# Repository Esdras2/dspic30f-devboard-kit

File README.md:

# dsPIC30F4011 / dsPIC33EP Dev Boards  
*A through-hole, single-supply platform for mixed-signal DSP labs*

> Compact, **breadboard-friendly** boards built around Microchip’s  
> **dsPIC30F4011 (DIP-40)** and **dsPIC33EP128MC206 (TQFP-64)**.  
> Ideal for university courses and hobbyists who need a low-cost, fully-THT solution for real-time DSP, motor-control, or instrumentation projects.

---

## 📑 Table of Contents
1. [Key Features (Rev D)](#key-features-rev-d)  
2. [Hardware Revisions](#hardware-revisions)  
3. [Folder Structure](#folder-structure)  
4. [Quick Start](#quick-start)  
5. [Bill of Materials](#bill-of-materials)  
6. [Pinout Reference](#pinout-reference)  
7. [Contributing](#contributing)  
8. [License](#license)  
9. [Resumen rápido en español](#resumen-rápido-en-español)

---

## Key Features (Rev D)

| Block            | Details                                                                                                     |
|------------------|-------------------------------------------------------------------------------------------------------------|
| **Power**        | 12 V DC barrel jack → **on-board 5 V LDO** (LM7805)                                                         |
| **CPU**          | **dsPIC30F4011** (DIP-40) or **dsPIC33EP128MC206** (TQFP-64, see docs)                                      |
| **Clock**        | Precise UART/DSP timing                                                                                     |
| **Reset**        | Single **RC + Schmitt trigger** → faster boot, ~50 % parts count cut                                        |
| **ICSP**         | Standard 6-pin header (Pickit 3/4 compatible)                                                               |
| **Service**      | **Bridge jumpers** isolate power, ICSP, and analog rails → safe bring-up / troubleshooting                   |
| **Silkscreen**   | Pin name on **every** MCU pad + labelled test points                                                        |
| **Form Factor**  | 52 mm × 45 mm PCB (≈18 % smaller than Rev B) — fits 70 mm breadboards                                       |

*Full schematic, 3-D renders, PDFs, and Gerbers live in `/hardware/Rev_D/`.*

---

## Hardware Revisions

| Rev | Focus                      | Major Changes                                                                                                          |
|-----|----------------------------|------------------------------------------------------------------------------------------------------------------------|
| **B** | First production           | Base THT design, 12 V→5 V regulation, full silkscreen                                                                  |
| **C** | Bug-fix & size reduction  | Fixed reversed barrel polarity, wired V<sub>REF±</sub>; **PCB shrunk** 63 × 52 mm → 52 × 45 mm                          |
| **D** | Serviceability & accuracy | Simplified reset, **larger socket pads**, bridge jumpers, **crystal oscillator added**                                 |

*Older spins remain for reference; **Rev D** is the recommended build.*

---

## Folder Structure
```text
.
├── hardware/         # KiCad 8 projects
│   ├── Rev_B/
│   ├── Rev_C/
│   └── Rev_D/
├── firmware/         # MPLAB X XC16 demo code (blinky, UART loop-back, FIR demo)
├── docs/             # Schematics (PDF), BOMs (CSV/XLSX), 3-D STEP, pinouts
│   └── dspic33.cvs   # Pinout for dsPIC33EP128MC206
└── README.md
```

---

## Quick Start

### 1 · Clone & Open Hardware

```bash
git clone https://github.com/<your-org>/dsPIC30F4011-THT.git
cd dsPIC30F4011-THT/hardware/Rev_D
kicad Rev_D.kicad_pro    # KiCad ≥ 8.0
```

### 2 · Generate Gerbers

KiCad → **File ▸ Plot** → select *Gerber* + *Drill*; zip and send to JLCPCB / PCBWay / OSH Park.

### 3 · Assemble

All parts are **through-hole**; ideal for hand-soldering or wave machines.  
*Tip :* keep bridge jumpers **open** on first power-up.

### 4 · Flash the Demo

TBD

---

## Bill of Materials (excerpt)

| Qty | Designator | Part & Link         | Note                 |
| --- | ---------- | ------------------- | -------------------- |
| 1   | U1         | dsPIC30F4011-I/P    | 40-pin DIP, 30 MIPS  |
| 1   | X1         | Crystal 7 .3728 MHz | HC-49S               |
| 2   | C7, C8     | 22 pF NP0           | Crystal load caps    |
| 1   | IC1        | LM7805              | TO-220, 1 A          |
| 8   | C1…C8      | 100 nF MLCC         | Decoupling (per VDD) |

*See* `docs/BOM_Rev_D.xlsx` *for the full list with supplier SKUs.*

---

## Pinout Reference

- **dsPIC30F4011**: See schematic and silkscreen.
- **dsPIC33EP128MC206**:  
  Pinout available in [`docs/dspic33.cvs`](docs/dspic33.cvs):

  ```
  1,(RA7)
  2,(RB14)
  3,(RB15)
  ...
  64,(RA10)
  ```

---

## Contributing
TBD

Bug reports and board mods are welcome!

---

## License

All hardware, firmware, and documents are released under the **MIT License**.  
See the [LICENSE](LICENSE) file for details.

---

## Resumen rápido (español)

* Placa educativa **THT** con **dsPIC30F4011** y soporte para **dsPIC33EP128MC206**.
* Rev D añade cristal, jumpers de aislamiento y pads más amplios.
* Archivos KiCad 8 en `/hardware/Rev_D/`; BOM completa y pinout en `docs/`.
* Programación vía ICSP con Pickit 3/4.

¡Felices prototipos! 🎉

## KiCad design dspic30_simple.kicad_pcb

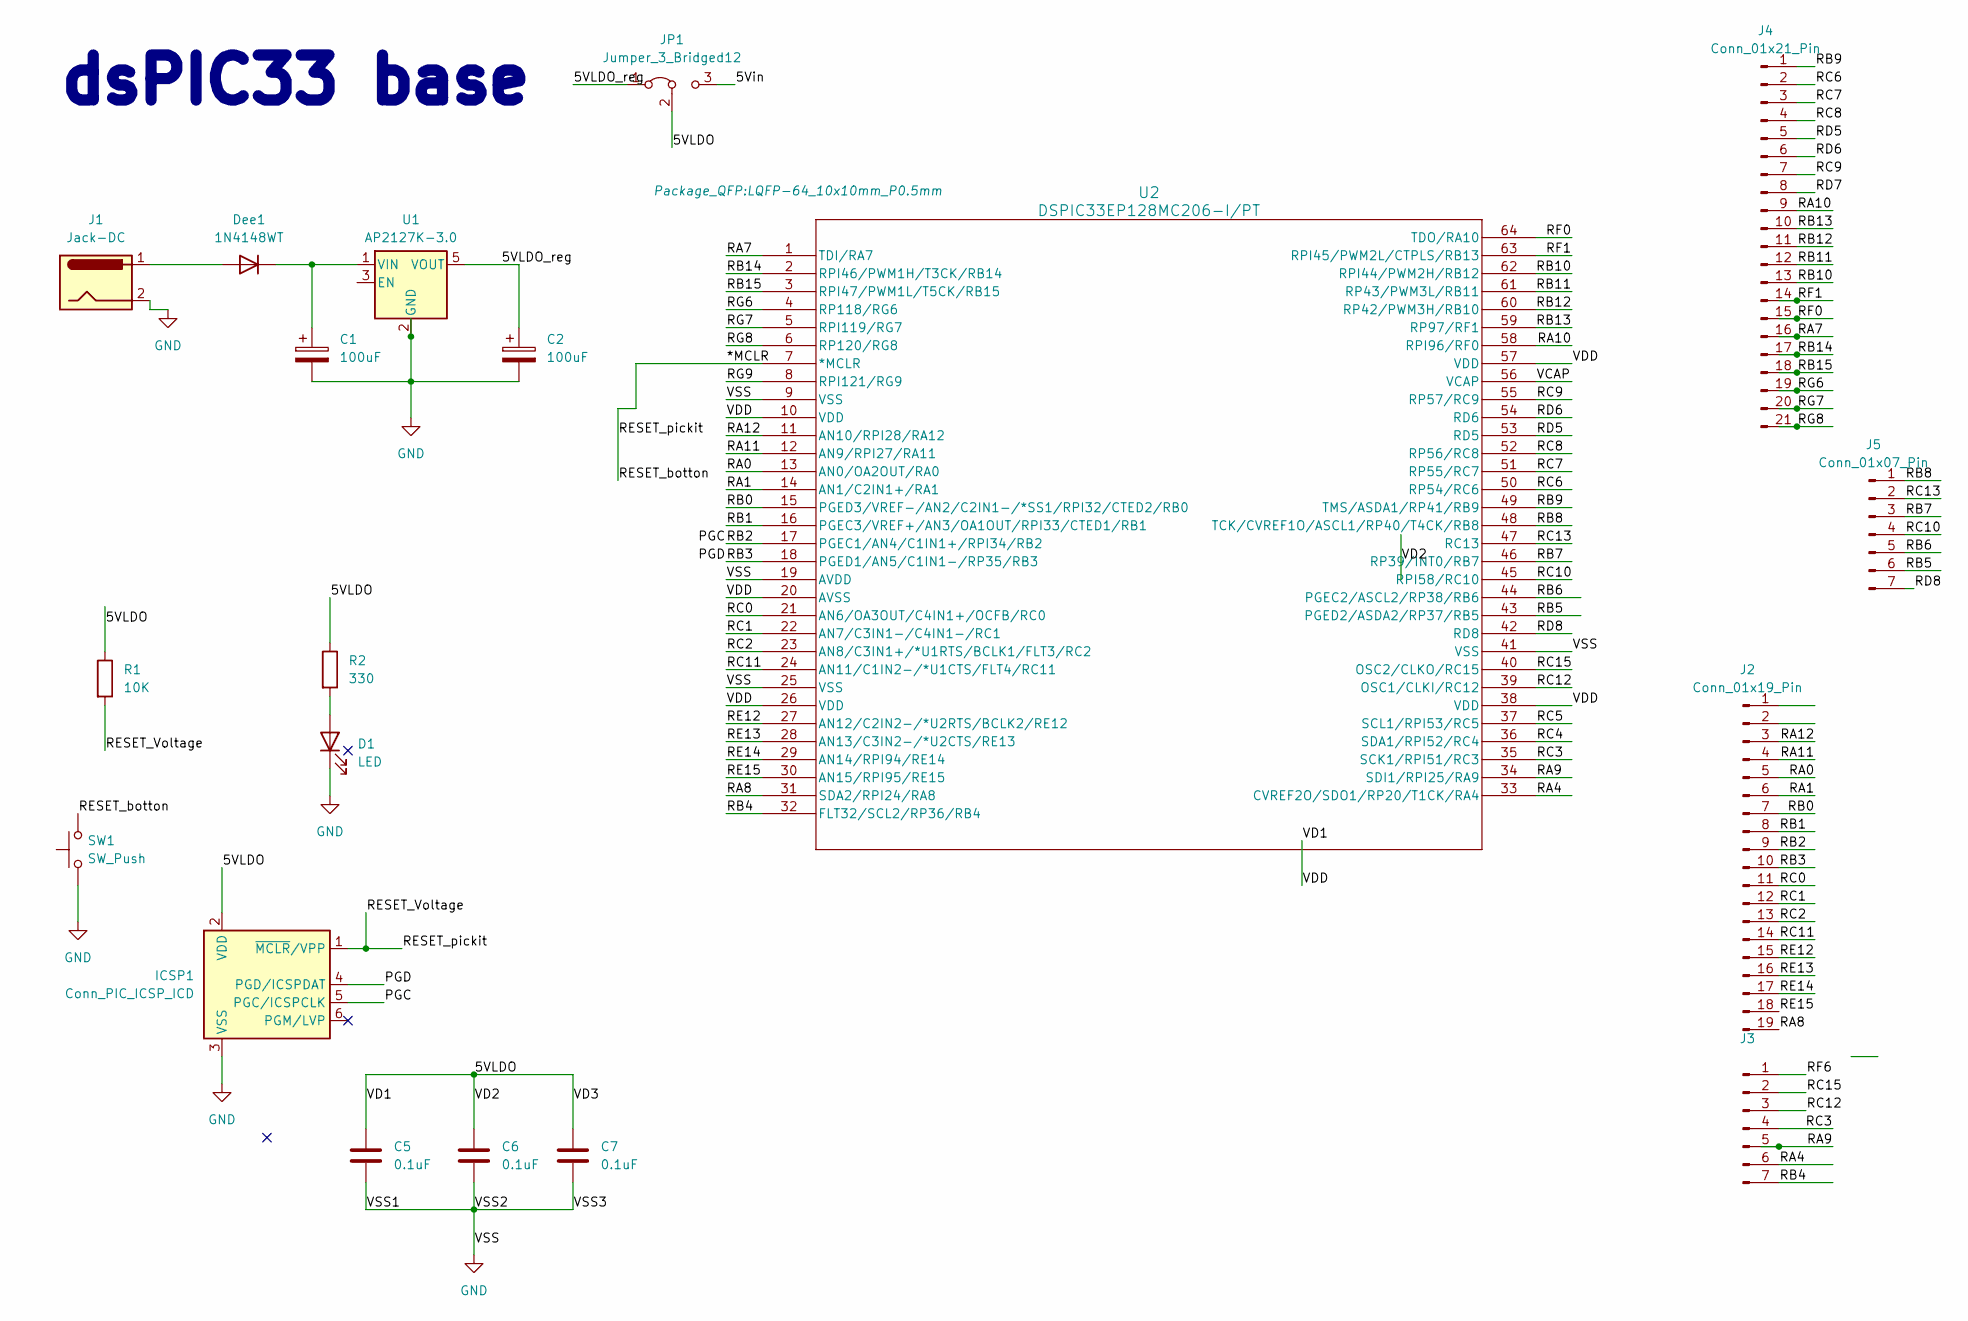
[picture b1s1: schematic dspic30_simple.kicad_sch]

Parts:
C1, C2: 100uF; CP_Elec_5x3
C5, C6, C7: 0.1uF; C_0402_1005Metric
D1: LED; LED_1206_3216Metric
Dee1: 1N4148WT; C_1206_3216Metric
ICSP1: Conn_PIC_ICSP_ICD; PinSocket_1x06_P2.54mm_Vertical
J1: Jack-DC; BarrelJack_GCT_DCJ200-10-A_Horizontal
J2: Conn_01x19_Pin; PinHeader_1x19_P2.54mm_Vertical
J3, J5: Conn_01x07_Pin; PinHeader_1x07_P2.54mm_Vertical
J4: Conn_01x21_Pin; PinHeader_1x21_P2.54mm_Vertical
JP1: Jumper_3_Bridged12; PinHeader_1x03_P2.54mm_Vertical
R1: 10K; R_0603_1608Metric
R2: 330; R_0603_1608Metric
SW1: SW_Push; SW_PUSH_6mm
U1: AP2127K-3.0; SOT-23-5
U2: DSPIC33EP128MC206-I/PT; LQFP-64_10x10mm_P0.5mm

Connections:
/5VLDO: C5.1, C6.1, C7.1, ICSP1.2 (VDD), JP1.2 (C), R1.1, R2.1, U2.10 (VDD), U2.20 (AVSS), U2.26 (VDD), U2.38 (VDD), U2.57 (VDD)
/5VLDO_reg: C2.1, JP1.1 (A), U1.5 (VOUT)
/5Vin: JP1.3 (B)
/*MCLR: ICSP1.1 (~MCLR/VPP), R1.2, SW1.2, U2.7 (*MCLR)
/PGC: ICSP1.5 (PGC/ICSPCLK), J2.9, U2.17 (PGEC1/AN4/C1IN1+/RPI34/RB2)
/PGD: ICSP1.4 (PGD/ICSPDAT), J2.10, U2.18 (PGED1/AN5/C1IN1-/RP35/RB3)
/RA0: J2.5, U2.13 (AN0/OA2OUT/RA0)
/RA1: J2.6, U2.14 (AN1/C2IN1+/RA1)
/RA4: J3.6, U2.33 (CVREF2O/SDO1/RP20/T1CK/RA4)
/RA7: J4.16, U2.1 (TDI/RA7)
/RA8: J2.19, U2.31 (SDA2/RPI24/RA8)
/RA9: J3.5, U2.34 (SDI1/RPI25/RA9)
/RA10: J4.9, U2.58 (RPI96/RF0)
/RA11: J2.4, U2.12 (AN9/RPI27/RA11)
/RA12: J2.3, U2.11 (AN10/RPI28/RA12)
/RB0: J2.7, U2.15 (PGED3/VREF-/AN2/C2IN1-/*SS1/RPI32/CTED2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)
/RB1: J2.8, U2.16 (PGEC3/VREF+/AN3/OA1OUT/RPI33/CTED1/RB1)
/RB4: J3.7, U2.32 (FLT32/SCL2/RP36/RB4)
/RB5: J5.6, U2.43 (PGED2/ASDA2/RP37/RB5)
/RB6: J5.5, U2.44 (PGEC2/ASCL2/RP38/RB6)
/RB7: J5.3, U2.46 (RP39/INT0/RB7)
/RB8: J5.1, U2.48 (TCK/CVREF1O/ASCL1/RP40/T4CK/RB8)
/RB9: J4.1, U2.49 (TMS/ASDA1/RP41/RB9)
/RB10: J4.13, U2.62 (RPI44/PWM2H/RB12)
/RB11: J4.12, U2.61 (RP43/PWM3L/RB11)
/RB12: J4.11, U2.60 (RP42/PWM3H/RB10)
/RB13: J4.10, U2.59 (RP97/RF1)
/RB14: J4.17, U2.2 (RPI46/PWM1H/T3CK/RB14)
/RB15: J4.18, U2.3 (RPI47/PWM1L/T5CK/RB15)
/RC0: J2.11, U2.21 (AN6/OA3OUT/C4IN1+/OCFB/RC0)
/RC1: J2.12, U2.22 (AN7/C3IN1-/C4IN1-/RC1)
/RC2: J2.13, U2.23 (AN8/C3IN1+/*U1RTS/BCLK1/FLT3/RC2)
/RC3: J3.4, U2.35 (SCK1/RPI51/RC3)
/RC4: U2.36 (SDA1/RPI52/RC4)
/RC5: U2.37 (SCL1/RPI53/RC5)
/RC6: J4.2, U2.50 (RP54/RC6)
/RC7: J4.3, U2.51 (RP55/RC7)
/RC8: J4.4, U2.52 (RP56/RC8)
/RC9: J4.7, U2.55 (RP57/RC9)
/RC10: J5.4, U2.45 (RPI58/RC10)
/RC11: J2.14, U2.24 (AN11/C1IN2-/*U1CTS/FLT4/RC11)
/RC12: J3.3, U2.39 (OSC1/CLKI/RC12)
/RC13: J5.2, U2.47 (RC13)
/RC15: J3.2, U2.40 (OSC2/CLKO/RC15)
/RD5: J4.5, U2.53 (RD5)
/RD6: J4.6, U2.54 (RD6)
/RD7: J4.8
/RD8: J5.7, U2.42 (RD8)
/RE12: J2.15, U2.27 (AN12/C2IN2-/*U2RTS/BCLK2/RE12)
/RE13: J2.16, U2.28 (AN13/C3IN2-/*U2CTS/RE13)
/RE14: J2.17, U2.29 (AN14/RPI94/RE14)
/RE15: J2.18, U2.30 (AN15/RPI95/RE15)
/RF0: J4.15, U2.64 (TDO/RA10)
/RF1: J4.14, U2.63 (RPI45/PWM2L/CTPLS/RB13)
/RF6: J3.1
/RG6: J4.19, U2.4 (RP118/RG6)
/RG7: J4.20, U2.5 (RPI119/RG7)
/RG8: J4.21, U2.6 (RP120/RG8)
/RG9: U2.8 (RPI121/RG9)
/VCAP: U2.56 (VCAP)
GND: C1.2, C2.2, C5.2, C6.2, C7.2, D1.1 (K), ICSP1.3 (VSS), J1.2, SW1.1, U1.2 (GND), U2.9 (VSS), U2.19 (AVDD), U2.25 (VSS), U2.41 (VSS)
unnamed: D1.2 (A), R2.2
unnamed: Dee1.2 (A), J1.1
unnamed: C1.1, Dee1.1 (K), U1.1 (VIN)

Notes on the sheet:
dsPIC33 base

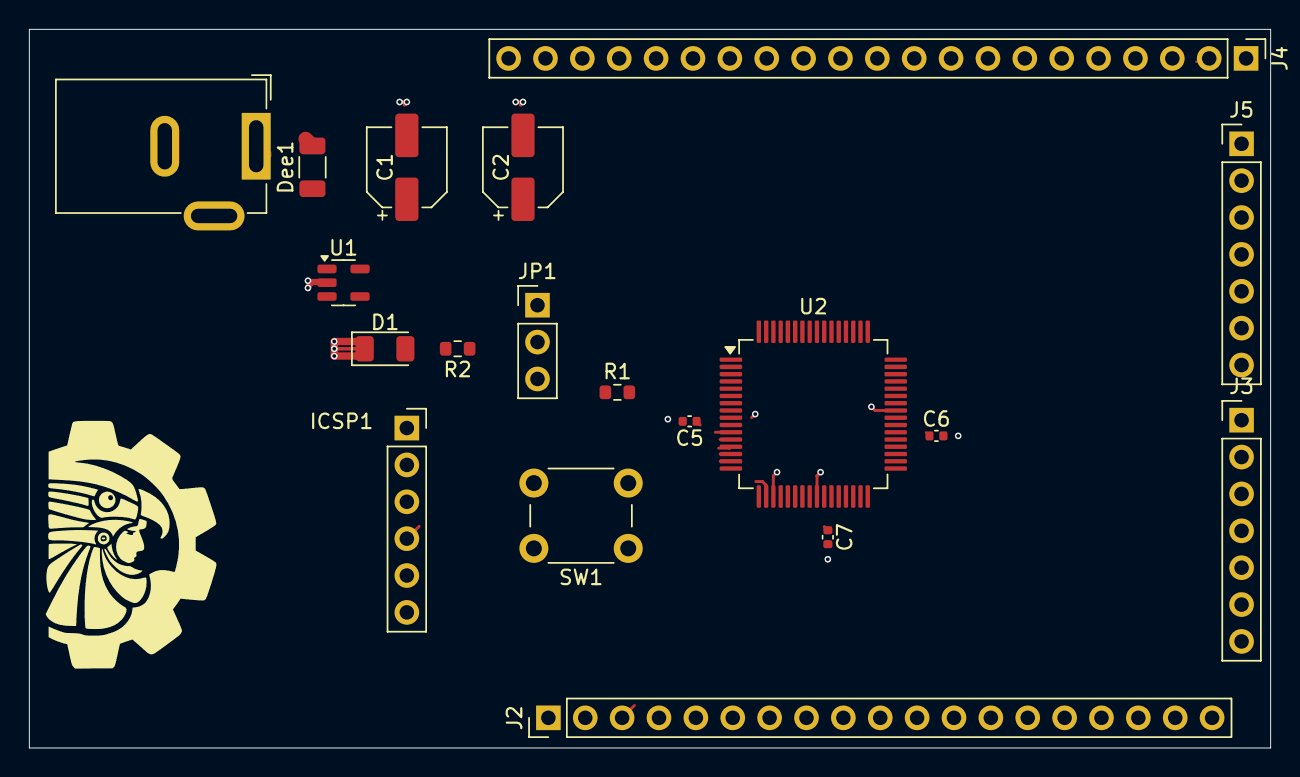
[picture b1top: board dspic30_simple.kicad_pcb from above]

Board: 2 copper layers, 85.5 x 49.5 mm, 19 parts (0 on the bottom side), 57 nets.

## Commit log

2025-03-20 init smd ended rev 0.1a
2025-03-20 initial rev 0.1b
2025-03-20 changes smd component for tht components
2025-03-20 fix GDN not connnected
2025-03-20 GND DRC warnings
2025-04-07 .gitignore: remove zip and gebber from repository
2025-05-02 fix conflicts
2025-06-08 revision rev D
2025-06-08 Create README.md
    Added first README version
2025-06-08 mejora de archivo gitignore
2025-06-08 se añade lista BOM de materiales
2025-06-08 Update README.md
    correction readme format
2025-06-08 remove no longer needed folder, files
2025-06-08 create license file
2025-06-11 adding docs/images
2025-07-16 feat(hw): bootstrap dsPIC33EP128MC206 dev‑kit (Rev A, pre‑rout)
    • Añadido “sistema mínimo” (LDO 3 V3, reset RC, ICSP, filtrado) para DSPIC33EP128MC206‑I/PT
    • Creado símbolo y asociado huella TQFP‑64 (0 .65 mm pitch)
    • Colocación preliminar de MCU, conectores de alimentación, ICSP y headers PPS
    • Asignadas/ajustadas huellas de todos los componentes (THT ↔ SMD)
    • Proyecto listo para fase de enrutado y “ERC/DRC clean” inicial
2025-07-16 modificacion del readme

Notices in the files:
README.md:
License: MIT
